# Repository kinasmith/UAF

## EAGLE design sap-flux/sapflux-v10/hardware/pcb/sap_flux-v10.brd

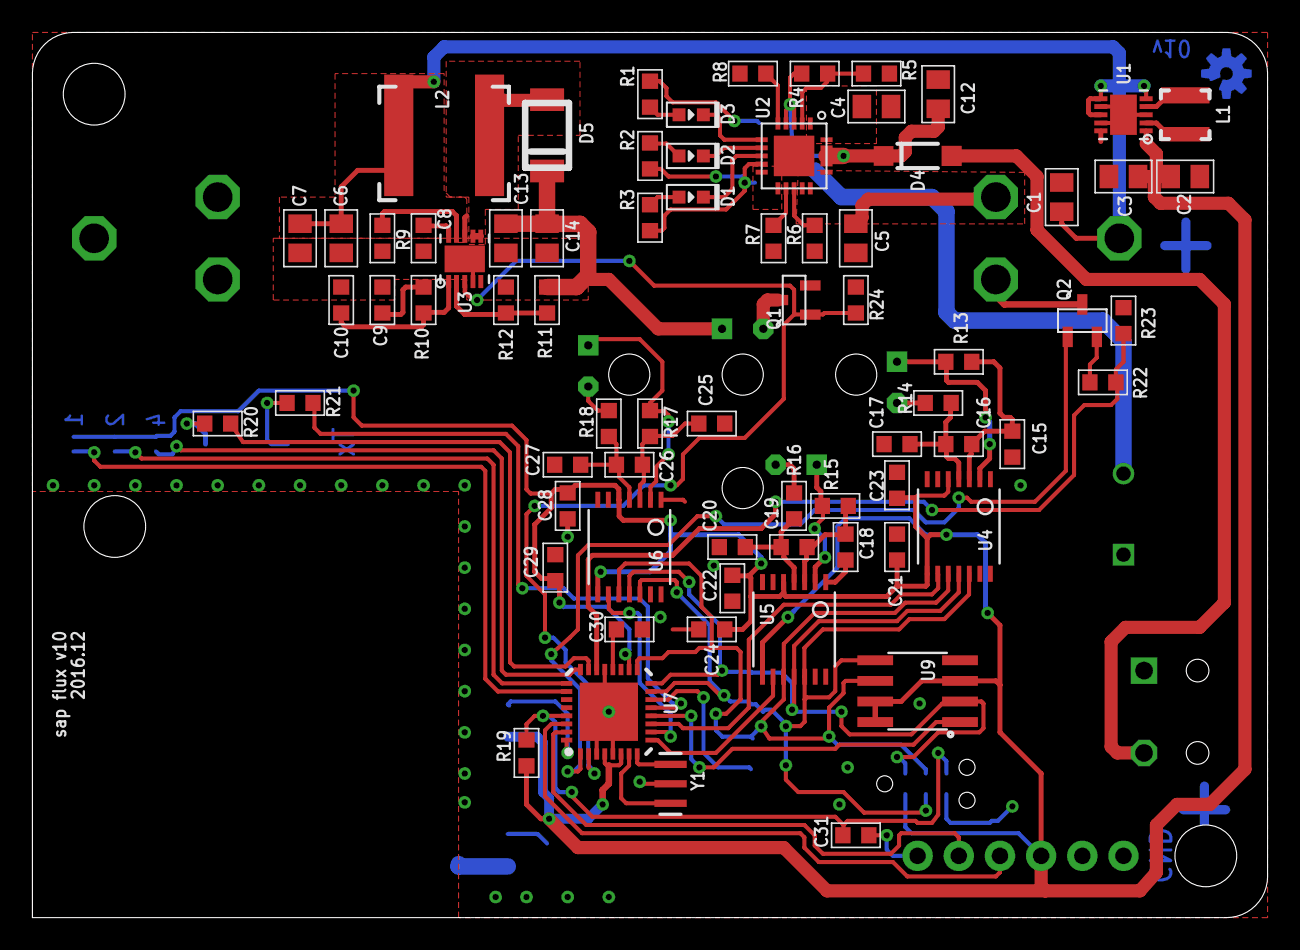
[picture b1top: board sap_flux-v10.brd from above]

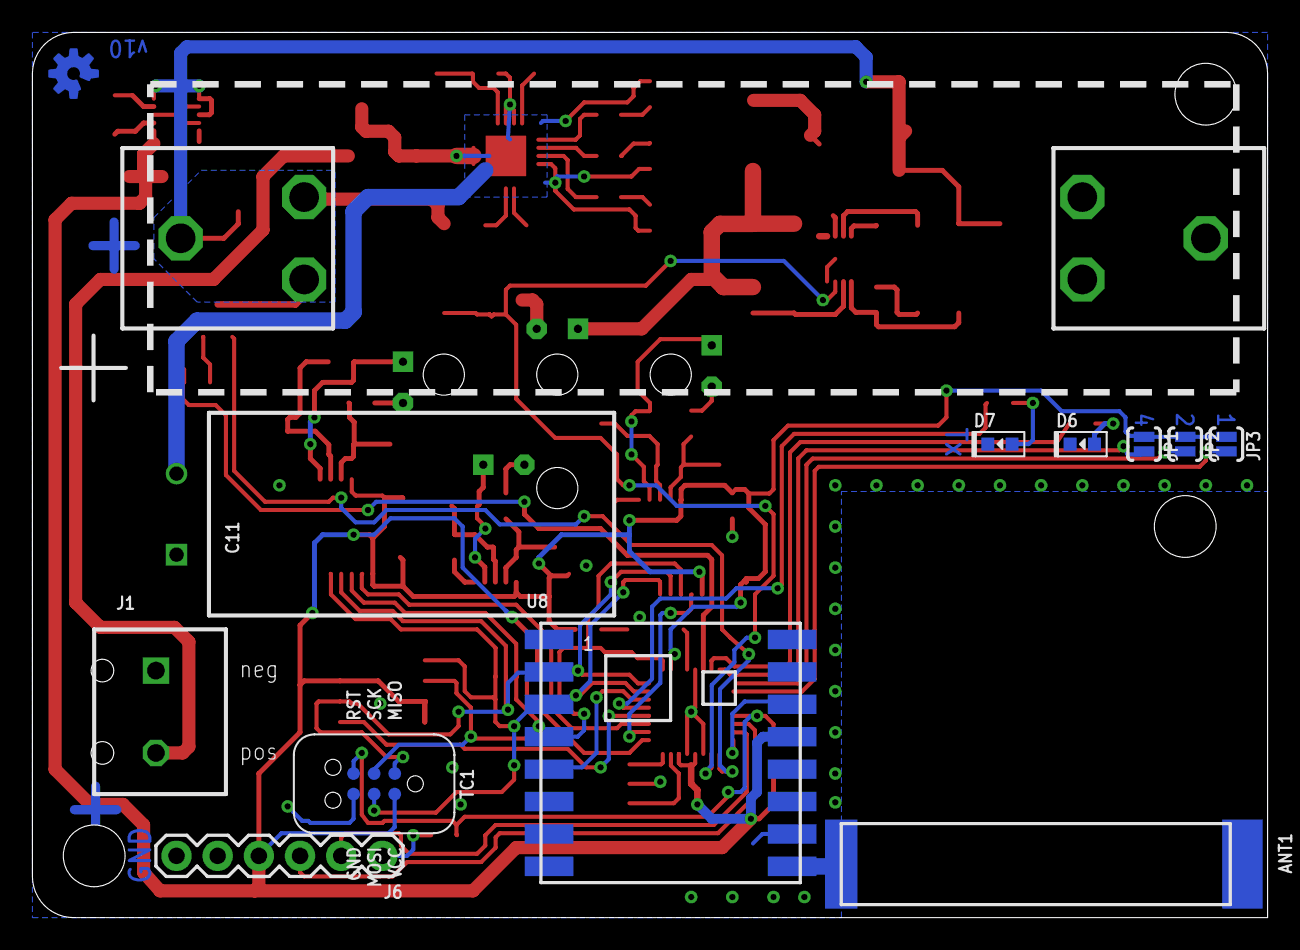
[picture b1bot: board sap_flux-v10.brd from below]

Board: 2 copper layers, 76.2 x 54.6 mm, 92 parts (13 on the bottom side), 66 nets.

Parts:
ANT1: ANTENNA-433_CHIP; ANT_433_CHIP
BATT1: BATTERY_HOLDER-18650_CLIP; BAT_18650_CLIP
C1, C2, C3, C4, C5, C6, C7, C12, C13, C14: 10uF; C0805-N
C8: 4700pF; C0603-N
C9: 2200pF; C0603-N
C10: 3300pF; C0603-N
C11: 4700uF; CP_TH_5MM
C15, C17, C18, C20, C25, C27: 0.01uF; C0603-N
C16, C19, C21, C22, C23, C24, C26, C28, C29, C30, C31: 0.1uF; C0603-N
D1, D2, D3: LED0603
D4: DIODE-SCHOTTKY-SOD123FL; SOD-123FL
D5: DIODE-SCHOTTKY-SOD128; SOD128
D6: green; LED0603
D7: red; LED0603
FRAME1: FRAME-LETTER; CREATIVE_COMMONS
FRAME2, FRAME3: FRAME-LETTERNO_PACKAGE; DUMMY
J1: CON_01X02-0.2"_POL; 1X02_SCREWTERM_0.2IN
J2, J3, J4, J5: CON_01X02TINY; 1X02_TINY
J6: 1X06
JP1: 1; PAD-JUMPER-2-NO_YES_SILK
JP2: 2; PAD-JUMPER-2-NO_YES_SILK
JP3: 4; PAD-JUMPER-2-NO_YES_SILK
L1: 1.5uH; L3030
L2: 4.7uH 4.3A; L8080
LOGO1: OSHW-LOGOS-COPPER; OSHW-LOGO-S_COPPER
Q1: Nfet; SOT23-3
Q2: battery reading nfet; SOT23-3
R1, R2, R3, R20, R21: 1k; R0603-N
R4: 270k; R0603-N
R5, R7: 100k; R0603-N
R6, R8: 10k --CHECK THIS; R0603-N
R9: 66.5k; R0603-N
R10: 2k; R0603-N
R11: 42.2k; R0603-N
R12, R19, R24: 10k; R0603-N
R13, R14, R15, R16, R17, R18: 100; R0603-N
R22: 33k; R0603-N
R23: 68k; R0603-N
TC1: TC2030-IDC-NL
U1: ADP2503; DFN300X300X80-11N
U2: QFN20
U3: ADP1614; DFN300X300X80-11N
U4, U5, U6: MAX31856MUD+; TSSOP14
U7: ATMEGA328P_32PIN-MU; MLF32_RECTPADS
U8: RFM69HCW-433MHZ; RFM69HCW-XXXS2
U9: WINBOND_FLASH_4MBIT-SOIC; SOIC8
Y1: 8MHZ; RESONATOR-SMD

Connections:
3V3: C2.1, C3.1, C21.2, C22.2, C23.2, C24.2, C28.2, C29.2, J6.4, JP1.1, JP2.1, JP3.1, R19.1, TC1.P$2, U1.1, U1.10, U4.5, U4.8, U5.5, U5.8, U6.5, U6.8, U7.4, U7.6, U7.18, U8.13, U9.3, U9.7, U9.8
6V5: C13.2, C14.1, D5.C-1, J2.NEG, R11.2
6V5_INDUCTOR: D5.A-2, L2.2, U3.6, U3.7
BAT_V_EN: Q2.1, U7.1
BAT_V_READ: R22.1, R23.2, U7.22
FLASH_CS: U7.12, U9.1
GND: BATT1.NEG_1, BATT1.NEG_2, BATT1.NEG_3, C1.2, C2.2, C3.2, C4.2, C5.2, C6.1, C7.2, C8.2, C9.2, C10.2, C11.NEG, C12.2, C13.1, C14.2, C15.2, C17.1, C18.2, C20.1, C21.1, C22.1, C23.1, C24.1, C25.2, C27.1, C28.1, C29.1, C30.2, D6.CATHODE, D7.CATHODE, J1.NEG, J6.6, Q1.2, R5.1, R6.1, R7.1, R8.1, R9.2, R12.1, R23.1, R24.1, TC1.P$6, U1.3, U1.7, U1.9, U1.11, U2.10, U2.11, U3.4, U3.5, U3.11, U4.1, U4.14, U5.1, U5.14, U6.1, U6.14, U7.3, U7.5, U7.21, U7.PAD, U8.1, U8.8, U8.10, U9.4, Y1.2
HTR_EN: Q1.1, R24.2, U3.3, U7.2
MISO: TC1.P$1, U4.11, U5.11, U6.11, U7.16, U8.2, U9.2
MOSI: TC1.P$4, U4.12, U5.12, U6.12, U7.15, U8.3, U9.5
unnamed: J5.POS, R18.1
unnamed: J5.NEG, R17.1, U6.2
unnamed: J4.POS, R16.1
unnamed: J4.NEG, R15.1, U5.2
unnamed: D4.A, J1.POS
unnamed: D3.CATHODE, U2.6
unnamed: R4.1, R5.2, U2.2
unnamed: J3.POS, R14.1
unnamed: J3.NEG, R13.1, U4.2
unnamed: D2.CATHODE, U2.7
unnamed: D1.CATHODE, U2.8
unnamed: R6.2, U2.13
unnamed: R7.2, U2.12
unnamed: D3.ANODE, R1.1
unnamed: D2.ANODE, R2.1
unnamed: D1.ANODE, R3.1
unnamed: L1.P$1, U1.4
unnamed: L1.P$2, U1.2
unnamed: R8.2, U2.5
unnamed: J2.POS, Q1.3
unnamed: C8.1, U3.10
unnamed: R9.1, U3.9
unnamed: ANT1.1, U8.9
unnamed: Q2.2, R22.2
unnamed: R11.1, R12.2, U3.2
unnamed: R20.1, U7.23
unnamed: C10.1, R10.2, U3.1
unnamed: C9.1, R10.1
unnamed: C31.1, J6.1
unnamed: C19.1, C20.2, R16.2, U5.4
unnamed: C18.1, C19.2, R15.2, U5.3
unnamed: D7.ANODE, R21.2
unnamed: D6.ANODE, R20.2
unnamed: C16.1, C17.2, R14.2, U4.4
unnamed: C15.1, C16.2, R13.2, U4.3
unnamed: C25.1, C26.2, R17.2, U6.3
unnamed: C26.1, C27.2, R18.2, U6.4
unnamed: U7.8, Y1.3
unnamed: U7.7, Y1.1
unnamed: C30.1, U7.20
N_SEL1: JP1.2, U7.24
N_SEL2: JP2.2, U7.25
N_SEL3: JP3.2, U7.26
PIN_9: R21.1, U7.13
RF_CS: U7.14, U8.5
RF_INT: U7.32, U8.14
RST: C31.2, R19.2, TC1.P$5, U7.29
RX: J6.3, U7.30
SCK: TC1.P$3, U4.10, U5.10, U6.10, U7.17, U8.4, U9.6
TC1_CS: U4.9, U7.11
TC2_CS: U6.9, U7.10
TC3_CS: U5.9, U7.9
TX: J6.2, U7.31
V_BAT: BATT1.POS_1, BATT1.POS_2, BATT1.POS_3, C1.1, C5.1, C6.2, C7.1, L2.1, Q2.3, U1.5, U1.6, U1.8, U2.14, U2.15, U2.16, U3.8
V_LOAD: C4.1, U2.1, U2.20
V_SOLAR: C11.POS, C12.1, D4.C, R1.2, R2.2, R3.2, R4.2, U2.3, U2.4, U2.9, U2.17, U2.18, U2.19

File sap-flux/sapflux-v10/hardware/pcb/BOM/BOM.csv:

Supplier Part No,Mfg Part No,Mfg Name,Ref No,Quantity,Value,Description
712-1568-1-ND,0433AT62A0020E,Johanson Technology Inc.,ANT1 ,1,ANTENNA-433_CHIP,433MHz Chip RF Antenna 423MHz ~ 443MHz -4dBi Solder Surface Mount
36-54-ND,54,Keystone Electronics,BATT1 ,1,BATTERY_HOLDER-18650_CLIP,BATTERY CLIP 18MM 18650 CELL
490-6473-1-ND,GRM21BR61C106KE15K,Murata Electronics North America,C1 C2 C3 C4 C5 C6 C7 C12 C13 C14 ,10,10uF,10µF ±10% 16V Ceramic Capacitor X5R 0805 (2012 Metric)
490-11515-1-ND,GRM188R71C472KA01D,Murata Electronics North America,C8 ,1,4700pF,4700pF ±10% 16V Ceramic Capacitor X7R 0603 (1608 Metric)
490-11512-1-ND,GRM188R71C222KA01D,Murata Electronics North America,C9 ,1,2200pF,2200pF ±10% 16V Ceramic Capacitor X7R 0603 (1608 Metric)
399-9065-1-ND,C0603C332K4RACTU,Murata Electronics North America,0C10 ,1,3300pF,3300pF ±10% 16V Ceramic Capacitor X7R 0603 (1608 Metric)
P5130-ND,ECA-1AM472,Panasonic Electronic Components,1C11 ,1,4700uF,"4700µF 10V Aluminum Capacitors Radial, Can 2000 Hrs @ 85¡C"
490-1525-1-ND,GRM188R71C103KA01D,Murata Electronics North America,5C15 C17 C18 C20 C25 C27 ,6,0.01uF,10000pF ±10% 16V Ceramic Capacitor X7R 0603 (1608 Metric)
311-1088-1-ND,CC0603KRX7R7BB104,Yageo,6C16 C19 C21 C22 C23 C24 C26 C28 C29 C30 C31 ,11,0.1uF,0.10µF 16V Ceramic Capacitor X7R 0603 (1608 Metric)Ê
160-1447-1-ND,LTST-C191KRKT,Lite-On Inc.,D1 D2 D3 D7 ,4,,Red 631nm LED Indication - Discrete 2V 0603Ê
MBR120VLSFT1GOSCT-ND,MBR120VLSFT1G,ON Semiconductor,D4 ,1,DIODE-SCHOTTKY-SOD123FL,Diode Schottky 20V 1A Surface Mount SOD-123FL
CMS05QMCT-ND,"CMS05(TE12L,Q,M)",Toshiba Semiconductor and Storage,D5 ,1,DIODE-SCHOTTKY-SOD128,Diode Schottky 30V 5A Surface Mount M-FLAT (2.4x3.8)
160-1446-1-ND,LTST-C191KGKT,Lite-On Inc.,D6 ,1,green,Green 571nm LED Indication - Discrete 2V 0603 (1608 Metric)
WM13976-ND,0398890042,"Molex, LLC",J1 ,1,"CON_01X02-0.2_POL""","2 Position Wire to Board Terminal Block Horizontal with Board 0.200"" (5.08mm) Through Hole"
609-3272-ND,68001-106HLF,Amphenol FCI,J6 ,1,,"6 Positions Header, Unshrouded Connector 0.100"" (2.54mm) Through Hole Gold or Gold, GXTª"
587-2617-1-ND,NR3015T1R5N,Taiyo Yuden,L1 ,1,1.5uH,1.5µH Shielded Wirewound Inductor 1.82A 48 mOhm Max Nonstandard
587-2972-1-ND,NRS8040T100MJGJ,Taiyo Yuden,L2 ,1,4.7uH 4.3A,10µH Shielded Wirewound Inductor 3.1A 44.2 mOhm Max Nonstandard
DMN2075U-7DICT-ND,DMN2075U-7,Diodes Incorporated,Q1 ,1,Nfet,MOSFET N-CH 20V 4.2A SOT23
SI2312BDS-T1-GE3CT-ND,SI2312BDS-T1-GE3,Vishay Siliconix,Q2 ,1,battery reading nfet,MOSFET N-CH 20V 3.9A SOT23-3
311-1.00KHRCT-ND,RC0603FR-071KL,Yageo,R1 R2 R3 R20 R21 ,5,1k,RES SMD 1K OHM 1% 1/10W 0603
311-270KHRCT-ND,RC0603FR-07270KL,Yageo,R4 ,1,270k,RES SMD 270K OHM 1% 1/10W 0603
311-100KHRCT-ND,RC0603FR-07100KL,Yageo,R5 R7 ,2,100k,RES SMD 100K OHM 1% 1/10W 0603
311-10.0KHRCT-ND,RC0603FR-0710KL,Yageo,R6 R8 R12 R19 R24 ,5,10k --CHECK THIS,RES SMD 10K OHM 1% 1/10W 0603
311-66.5KHRCT-ND,RC0603FR-0766K5L,Yageo,R9 ,1,66.5k,RES SMD 66.5K OHM 1% 1/10W 0603
311-2.00KHRCT-ND,RC0603FR-072KL,Yageo,0R10 ,1,2k,RES SMD 2K OHM 1% 1/10W 0603
311-42.2KHRCT-ND,RC0603FR-0742K2L,Yageo,1R11 ,1,42.2k,RES SMD 42.2K OHM 1% 1/10W 0603
311-100HRCT-ND,RC0603FR-07100RL,Yageo,3R13 R14 R15 R16 R17 R18 ,6,100,RES SMD 100 OHM 1% 1/10W 0603
311-33.0KHRCT-ND,RC0603FR-0733KL,Yageo,2R22 ,1,33k,RES SMD 33K OHM 1% 1/10W 0603
311-68.0KHRCT-ND,RC0603FR-0768KL,Yageo,3R23 ,1,68k,RES SMD 68K OHM 1% 1/10W 0603
ADP2503ACPZ-3.3-R7CT-ND,ADP2503ACPZ-3.3-R7,Analog Devices Inc.,U1 ,1,ADP2503,"Buck-Boost Switching Regulator IC Positive Fixed 3.3V 1 Output 1A (Switch) 10-WFDFN Exposed Pad, CSP"
MCP73871-2AAI/ML,MCP73871-2AAI/ML-ND,Microchip Technology,U2 ,1,,Charger IC Lithium-Ion/Polymer 20-QFN-EP (4x4)
ADP1614ACPZ-650-R7CT-ND,ADP1614ACPZ-650-R7,Analog Devices Inc.,U3 ,1,ADP1614,"Boost Switching Regulator IC Positive Adjustable 2.5V 1 Output 4A (Switch) 10-WFDFN Exposed Pad, CSP"
MAX31856MUD+-ND,MAX31856MUD+,Maxim Integrated,U4 U5 U6 ,3,MAX31856MUD+,IC CONV THERMOCOUPLE 14TSSOP
ATMEGA328P-MU-ND,ATMEGA328P-MU,Atmel,U7 ,1,ATMEGA328P_32PIN-MU,AVR AVR¨ ATmega Microcontroller IC 8-Bit 20MHz 32KB (16K x 16) FLASH 32-VQFN (5x5)
1568-1391-ND,COM-13910,SparkFun Electronics,U8 ,1,RFM69HCW-433MHZ,RFM69HCW WIRELESS TRANSCEIVER 433MHZ
W25X40CLSNIG-ND,W25X40CLSNIG,Winbond Electronics,U9 ,1,WINBOND_FLASH_4MBIT-SOIC,IC FLASH 4MBIT 104MHZ 8SOIC
490-1195-1-ND,CSTCE8M00G55-R0,Murata Electronics North America,Y1 ,1,8MHZ,8MHz Ceramic Resonator Built in Capacitor 33pF ±0.2% -20¡C ~ 80¡C Surface Mount

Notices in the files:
parts and their libraries:
My_Aesthetics: Released under the Creative Commons Attribution Share-Alike 4.0 License
My_Aesthetics: https://creativecommons.org/licenses/by-sa/4.0
